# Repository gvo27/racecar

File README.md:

Preview images for PR bodies (rendered by make mech-build). Not a code branch.

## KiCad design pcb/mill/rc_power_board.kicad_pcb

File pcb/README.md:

# PCB projects (power distribution board)

KiCad 10 projects of the power distribution board: one battery feeds the compute, sensor and servo rails. The active board is [`src/`](src/) (the lab-mill board, next release rev3).

| Path | Content |
| --- | --- |
| `releases/rev1/` | The rev1 board, the base board: KiCad project (`rc_power_board.kicad_sch`, `.kicad_pcb`, `.kicad_pro`, `.kicad_dru`), lib tables, `bom.csv` (from `make bom`), schematic plot, `placement.py`, `design_rules.toml` |
| `releases/rev2/` | Rev2 release: a frozen copy of the mill prototype with the JST XH headers, with its own `design_rules.toml` (2026-11-17). Do not tune it |
| `src/` | The mill prototype (now with temporary wire solder pads for the first print round, `[parts.wire]` of the mill tuning file): the rev1 circuit without the LEDs and their resistors, with through-hole capacitors for C2 to C8, and with wider tracks and gaps for the lab mill. Made by `make pcb-all BOARD=src` from `src/placement.py` and the mill tuning file (`design_rules.toml` in the lab directory). Its next release is `releases/rev3/` |
| `lib/` | Symbol and footprint libraries, shared by all boards (`rc_power.kicad_sym`, `rc_power.pretty/`) |
| `libraries/` | Board tools, their Python libraries and tests. They run in the KiCad image through `make`. `paths.py` holds this layout |
| `COLCON_IGNORE` | Keeps this directory out of the ROS 2 build |

- The only deliverable of each board is its `.kicad_pcb` file (scope: `docs/pcb/conventions.md`). Fab outputs are optional and not committed. `make pcb-fab` writes them to `build/fab/<BOARD>/`.
- Context of the board and the schematic (plan, overview, BOM notes, review record): [`docs/pcb/`](../docs/pcb/README.md). Stale docs: `docs/archive/pcb/`.
- Releases are numbered `rev1`, `rev2`, `rev3` and so on (rev1 and rev2 were `rev_A` and `rev_B` until 2026-11-18). A release is frozen: copy the working board to `releases/rev<N>/` with its own `design_rules.toml`.
- Risks of the mill board, most important first: [review record](../docs/pcb/releases/rev3/review/README.md#risks-most-important-first).
- Lab facts, mill tools and waivers: the lab directory (`dir` in [`config/lab.toml`](config/lab.toml)).
- Rules: [`.claude/rules/schematics.md`](../.claude/rules/schematics.md).
- Design rules: `design_rules.toml` in the board directory, or in the lab directory for a board without its own file (`src/`). `make pcb-rules BOARD=<board>` checks the KiCad project files against them.
- Make targets: `make help`. A target works on one board: `make pcb-check BOARD=<path below pcb/>`. The default is the base board (`BASE_BOARD` in the Makefile, `DEFAULT_BOARD` in `libraries/paths.py`).

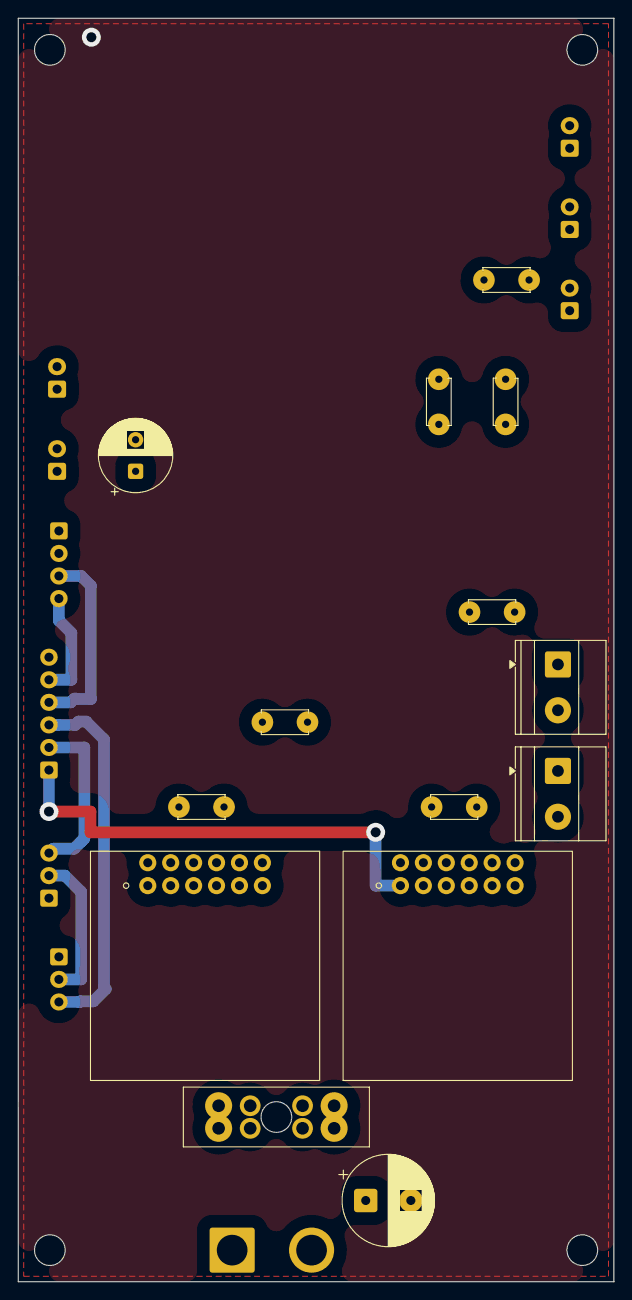
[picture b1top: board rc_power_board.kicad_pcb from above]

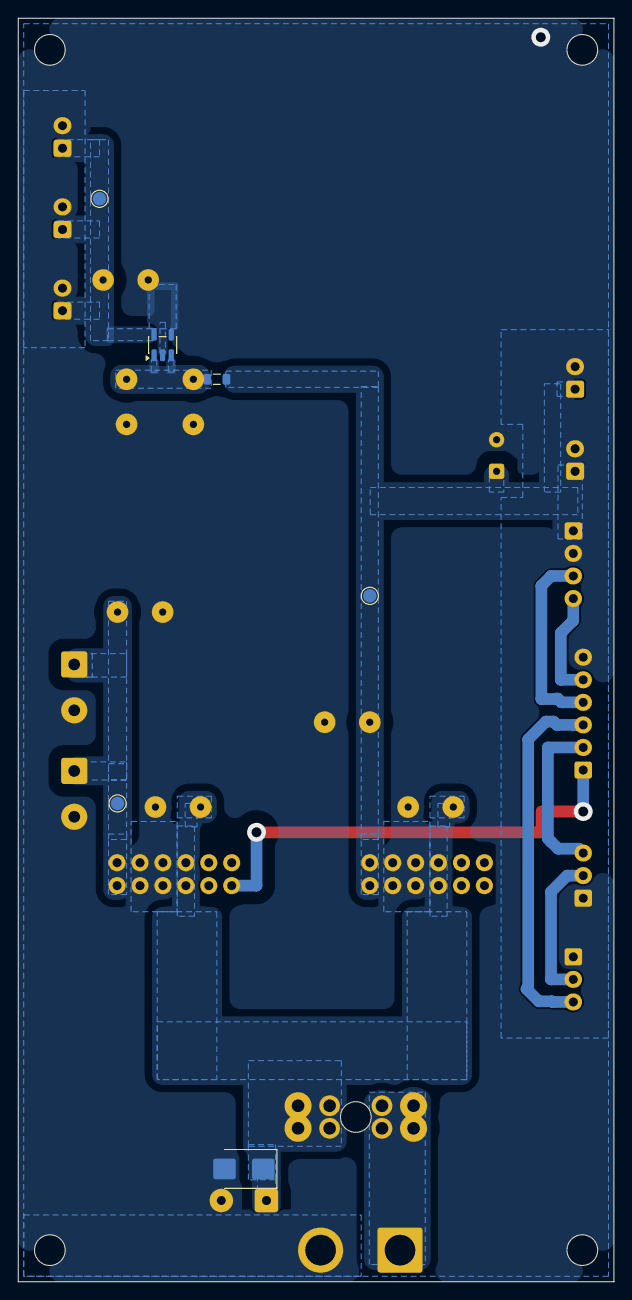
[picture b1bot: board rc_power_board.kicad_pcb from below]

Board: 2 copper layers, 66.0 x 140.0 mm, 34 parts (6 on the bottom side), 13 nets.

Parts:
C1: TBD uF >=16V; CP_Radial_D10.0mm_P5.00mm
C2, C4: TBD >=16V; C_Disc_D5.0mm_W2.5mm_P5.00mm
C3, C5: TBD >=10V; C_Disc_D5.0mm_W2.5mm_P5.00mm
C6: TBD filter; C_Disc_D5.0mm_W2.5mm_P5.00mm
C7, C8: 1uF TBD; C_Disc_D5.0mm_W2.5mm_P5.00mm
C9: TBD >=100uF low-ESR >=10V; CP_Radial_D8.0mm_P3.50mm
D1: TVS >=9V TBD; D_SMB
F1: TBD ATO/ATC blade 15A; FuseHolder_Blade_ATO_Littelfuse_FLR_178.6165
FB1: TBD filter; L_0805_2012Metric
H1, H2, H3, H4: MountingHole_M3; MountingHole_3.2mm_M3
J1: Battery T-plug pigtail 12AWG; SolderWire-2.5sqmm_1x02_P8.8mm_D2.4mm_OD4.4mm
J3: ESC Rx lead (BEC out, throttle in); SolderWire_1x03_P2.50mm
J4: Servo DS3225MG; SolderWire_1x03_P2.50mm
J5: Signals to ESP32; SolderWire_1x06_P2.50mm
J6: USB-C Pi 5; TerminalBlock_Phoenix_MKDS-1,5-2-5.08_1x02_P5.08mm_Horizont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
J7: USB-C ESP32; TerminalBlock_Phoenix_MKDS-1,5-2-5.08_1x02_P5.08mm_Horizont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
J8: LIDAR-Lite v4; SolderWire_1x04_P2.50mm
J9: Camera USB hub; SolderWire_1x02_P2.50mm
J11: Slamtec Mapper (5V); SolderWire_1x02_P2.50mm
J12: IMU; SolderWire_1x02_P2.50mm
J13: Shaft encoder; SolderWire_1x02_P2.50mm
J14: Spare 3.3V; SolderWire_1x02_P2.50mm
TP1: +5V_CPU; TestPoint_Pad_D1.5mm
TP2: +5V_SENS; TestPoint_Pad_D1.5mm
TP3: +3V3_SENS; TestPoint_Pad_D1.5mm
U1, U2: Pololu D36V50F5; Pololu_D36V50Fx
U3: AP2112K-3.3 (>=300 mA LDO, TBD); SOT-23-5

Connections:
+3V3_SENS: C8.1, J12.1, J13.1, J14.1, TP3.1, U3.5
+5V_CPU: C3.1, J6.1, J7.1, TP1.1, U1.11, U1.12
+5V_SENS: C5.1, C9.1, FB1.1, J8.1, J9.1, J11.1, TP2.1, U2.11, U2.12
+6V_BEC: J3.2, J4.2
/I2C_SCL: J5.5, J8.4
/I2C_SDA: J5.4, J8.3
/LDO_IN: C6.1, C7.1, FB1.2, U3.1, U3.3
/STEER_PWM: J4.3, J5.3
/THROTTLE_PWM: J3.3, J5.2
/U1_PG: J5.1, U1.1
/VBAT_RAW: F1.1, J1.1
GND: C1.2, C2.2, C3.2, C4.2, C5.2, C6.2, C7.2, C8.2, C9.2, D1.2, J1.2, J3.1, J4.1, J5.6, J6.2, J7.2, J8.2, J9.2, J11.2, J12.2, J13.2, J14.2, U1.7, U1.8, U1.9, U1.10, U2.7, U2.8, U2.9, U2.10, U3.2
VBAT: C1.1, C2.1, C4.1, D1.1, F1.2, U1.5, U1.6, U2.5, U2.6

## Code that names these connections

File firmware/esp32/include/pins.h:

#pragma once
// Pin map for ESP32-S3-N16R8 -- LEFT header (P1) only, see README.md.
// P1 order (USB ports at the bottom, chip facing you):
//   3V3 3V3 RST 4 5 6 7 15 16 17 18 8 3 46 9 10 11 12 13 14 5V G

// ---- Active (driven by this firmware) ----
constexpr int PIN_STEER_PWM    = 4;   // P1-4  -> DS3225 servo signal
constexpr int PIN_THROTTLE_PWM = 5;   // P1-5  -> THW-1060 ESC throttle signal
constexpr int PIN_I2C_SDA      = 8;   // P1-12 rangefinder pin 3 SDA; bus shared with IMU later
constexpr int PIN_I2C_SCL      = 9;   // P1-15 rangefinder pin 4 SCL; bus shared with IMU later

// ---- Reserved for future devices (NOT configured by this firmware) ----
constexpr int PIN_BATT_LOW     = 6;   // P1-6  battery hi/low digital in (ADC1_CH5 capable)
constexpr int PIN_IMU_INT      = 7;   // P1-7  6-axis IMU interrupt / data-ready
constexpr int PIN_ENC_A        = 15;  // P1-8  shaft encoder channel A (PCNT)
constexpr int PIN_ENC_B        = 16;  // P1-9  shaft encoder channel B (PCNT)
constexpr int PIN_SPARE_UART_TX = 17; // P1-10 spare (UART1 TX, alt. Pi link)
constexpr int PIN_SPARE_UART_RX = 18; // P1-11 spare (UART1 RX, alt. Pi link)
// Free: 10 (P1-16), 11 (P1-17), 12 (P1-18), 13 (P1-19), 14 (P1-20)

// ---- USB-C ports ----
// Left  "USB": native USB (GPIO19/20) -> planned regulated power input only
// Right "COM": CH343 -> UART0 (GPIO43/44) -> flashing + host link (laptop now, Pi later)
// ESP32 powers no peripherals; sensors use a separate regulated rail, common ground.

// ---- Do not use ----
// GPIO3  (P1-13): strapping pin (JTAG signal source)
// GPIO46 (P1-14): strapping pin (boot mode / ROM log)
// GPIO35-37: wired to octal PSRAM inside the module (right header)
// GPIO19/20: native USB D-/D+ (right header); GPIO43/44: UART0 -> CH343 "COM" port
